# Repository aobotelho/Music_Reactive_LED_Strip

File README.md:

# MusicReactiveLEDStrip
This is the repo for my music reactive LED Strip project
The first version is was made using a really cheap usb speaker board.
The second has an amplification stage using a 741 Op. Amp. for the audio amplification before the LED driving stage.

The three LED colors are driven after the amplified audio passes through a filter, so each of the LEDs is driven by different frequencies.

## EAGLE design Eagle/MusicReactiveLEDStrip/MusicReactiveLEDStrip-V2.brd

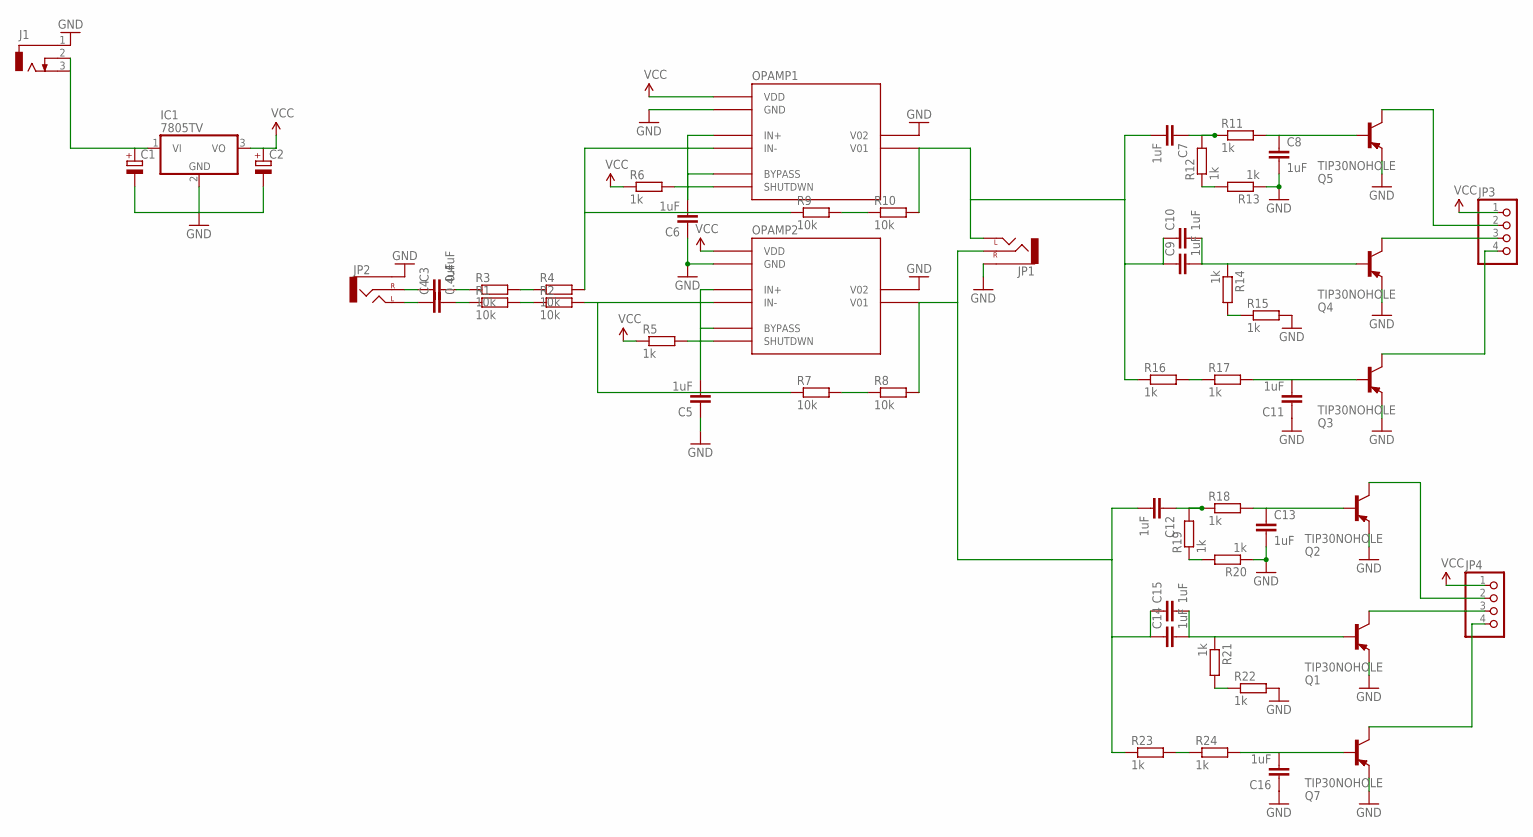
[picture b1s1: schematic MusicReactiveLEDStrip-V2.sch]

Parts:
C1, C2: CPOL-EUE2.5-6; E2,5-6
C3, C4: 0.4uF; C050-025X075
C5, C6, C7, C8, C9, C10, C11, C12, C13, C14, C15, C16: 1uF; C050-025X075
IC1: 7805TV; TO220V
J1: DCJ0303
JP1, JP2: AUDIO-JACKPTH; AUDIO-JACK
JP3, JP4: PINHD-1X4; 1X04
OPAMP1, OPAMP2: LM4871; SO08
Q1, Q2, Q3, Q4, Q5, Q7: TIP30NOHOLE; TO220-NOHOLE
R1, R2, R3, R4, R7, R8, R9, R10: 10k; 0207/10
R5, R6, R11, R12, R13, R14, R15, R16, R17, R18, R19, R20, R21, R22, R23, R24: 1k; 0207/10

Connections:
GND: C1.-, C2.-, C5.1, C6.1, C8.2, C11.1, C13.2, C16.1, IC1.2 (GND), J1.1, JP1.SLEEVE, JP2.SLEEVE, OPAMP1.7 (GND), OPAMP1.8 (V02), OPAMP2.7 (GND), OPAMP2.8 (V02), Q1.3 (E), Q2.3 (E), Q3.3 (E), Q4.3 (E), Q5.3 (E), Q7.3 (E), R13.1, R15.2, R20.1, R22.2
LEFT: OPAMP2.4 (IN-), R2.2, R7.1
LEFTOUT: C7.2, C9.1, C10.1, JP1.TIP (LEFT), OPAMP1.5 (V01), R10.2, R16.1
unnamed: R3.2, R4.1
unnamed: C3.1, JP2.RING (RIGHT)
unnamed: C3.2, R3.1
unnamed: C4.1, JP2.TIP (LEFT)
unnamed: C4.2, R1.1
unnamed: R1.2, R2.1
unnamed: OPAMP2.1 (SHUTDWN), R5.2
unnamed: C5.2, OPAMP2.2 (BYPASS), OPAMP2.3 (IN+)
unnamed: C6.2, OPAMP1.2 (BYPASS), OPAMP1.3 (IN+)
unnamed: OPAMP1.1 (SHUTDWN), R6.2
unnamed: R7.2, R8.1
unnamed: R9.2, R10.1
unnamed: C7.1, R11.1, R12.2
unnamed: R12.1, R13.2
unnamed: C8.1, Q5.1 (B), R11.2
unnamed: C12.1, R18.1, R19.2
unnamed: C9.2, C10.2, Q4.1 (B), R14.1
unnamed: R14.2, R15.1
unnamed: R16.2, R17.1
unnamed: C11.2, Q3.1 (B), R17.2
unnamed: R19.1, R20.2
unnamed: JP3.2, Q5.2 (C)
unnamed: JP3.3, Q4.2 (C)
unnamed: JP3.4, Q3.2 (C)
unnamed: C13.1, Q2.1 (B), R18.2
unnamed: C14.2, C15.2, Q1.1 (B), R21.1
unnamed: R21.2, R22.1
unnamed: R23.2, R24.1
unnamed: C16.2, Q7.1 (B), R24.2
unnamed: JP4.2, Q2.2 (C)
unnamed: JP4.3, Q1.2 (C)
unnamed: JP4.4, Q7.2 (C)
RIGHT: OPAMP1.4 (IN-), R4.2, R9.1
RIGHTOUT: C12.2, C14.1, C15.1, JP1.RING (RIGHT), OPAMP2.5 (V01), R8.2, R23.1
VCC: C2.+, IC1.3 (VO), JP3.1, JP4.1, OPAMP1.6 (VDD), OPAMP2.6 (VDD), R5.1, R6.1
VIN: C1.+, IC1.1 (VI), J1.2, J1.3

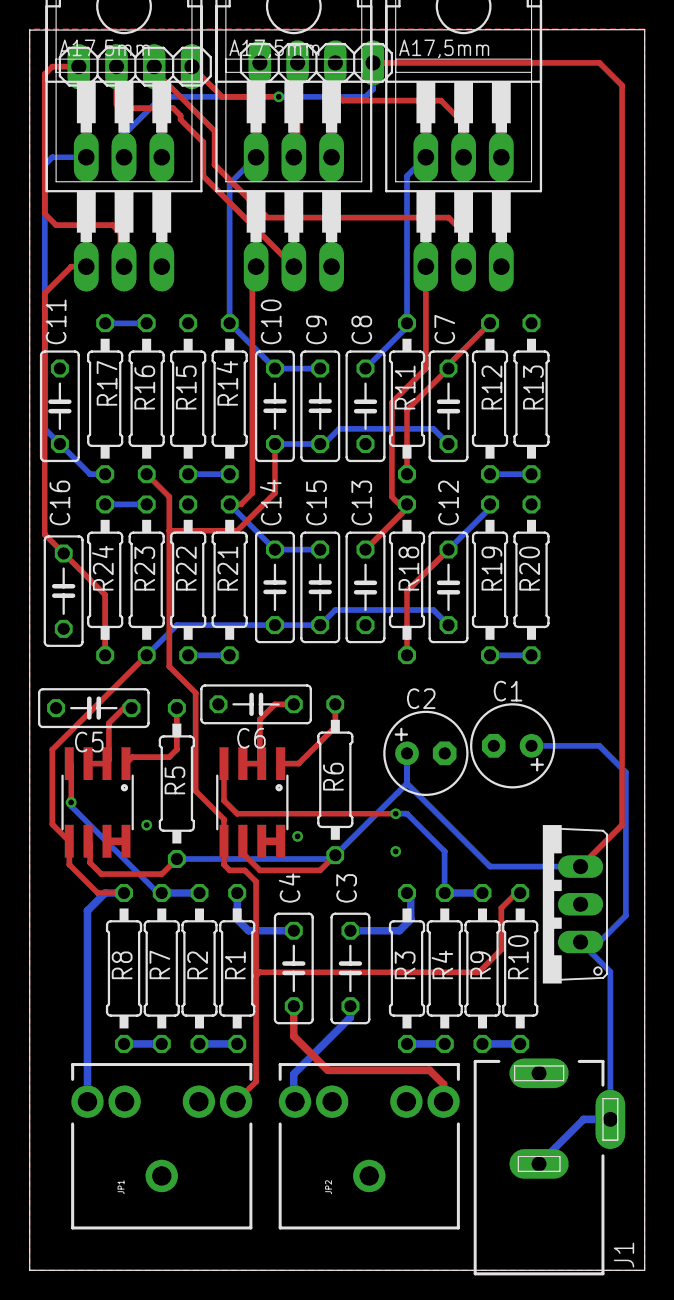
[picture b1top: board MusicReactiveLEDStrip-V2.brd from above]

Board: 2 copper layers, 41.4 x 83.5 mm, 54 parts (0 on the bottom side), 39 nets.

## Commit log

2017-08-25 Fixed typo
2017-11-29 Added board again. Dont f*&&* it up again, Andre

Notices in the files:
parts and their libraries:
SparkFun-Connectors: Licensing: Creative Commons ShareAlike 4.0 International - https://creativecommons.org/licenses/by-sa/4.0
